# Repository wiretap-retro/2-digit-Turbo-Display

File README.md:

# 2 digit Turbo Display
This project is a ATTiny85-based turbo display for retro PC's. It displays 2 digits, for use in 8088 to 486 systems.

## Intro
I was wanting to do an ATTiny85 project and came up with a small 2-digit turbo display for use in my Intel 486 retro gaming PC. This design is pretty simple, easy to build and easy to program. If you have a dead turbo display or your case is missing one, this might be the right fit, as I have tested it on 3 different cases I have and it fits perfect into all of them. Mounting holes are different in nearly every case, so another mounting method may be necessary depending on your situation.
<br /><br />
Demo Video: https://youtu.be/Jka8PfParP4

## Building
* Order the PCB through your PCB fab of choice. (JLCPCB, PCBway, OSH Park, etc.)
* Order the components as listed in the BOM. Substitutions may be necessary depending on the chip/component shortages.
* On the back side and front side, solder the surface mount components first. Pay close attention to the orientation of the SOIC chips, as they are reversed from each other on the right and left.
* On the back side, solder the through-hole components next. I recommend using a socket for the ATTiny85 so you can easily install/remove it for programming.
* On the front side, solder the LED 7-segment displays.
* Soldering complete. Go to the Programming section below.

## Programming
I have included the turbo.ino file as an example. In the main program loop, you can change the "normal" and "turbo" variables to any 2 digit number to match the needs of your particular CPU speeds. The code is pretty well commented, so you can play around with it, adjust delays, make a startup animation, etc. To program the ATTiny85, you can look at one of the hundreds of guides online. For mine, I used a breadboard and another Arduino to do so. After it is programmed, place it in the DIP-8 socket of the turbo display PCB.

## Installation
* As noted in the intro section, this was designed to fit in the Baby-AT cases I have. It seems there was no standard back in the day for making these turbo displays or mounting them, so each case can be different. The digit size fits all mine that have 2-digit display holes, and at least one mounting hole fits on two of the cases. Only one screw is really necessary anyway since it is so small and light. You can secure it in your case with various methods. (tape, blu tack, 3d printed clip, etc.)
* Once mounted in the case, connect the 5V power to a Berg/Molex-->2x2.54mm header. 
* Connect the Turbo LED on your case to the TLED OUT pins.
* Use a female to female cable with 2x2.54mm connectors at each end to connect the motherboard's Turbo LED pins to the turbo display board's TLED IN. These are commonly found on Aliexpress, Amazon, and Ebay for use in Arduino/RPi projects.
* The turbo switch on your case should be connected to the computer's motherboard Turbo Switch pins.
* Turn on the PC and test it out!

## Design Notes
The design takes into account that your motherboard has turbo LED pins to drive switching of this display. I found this to be the most common feature among all motherboards, from the 8088 to 486. I probably own 25 different boards of this era, and they all have the pins to drive a turbo LED. This is the most universal design I could come up with.

## Other
This is an open source project. Feel free to do what you want with it.

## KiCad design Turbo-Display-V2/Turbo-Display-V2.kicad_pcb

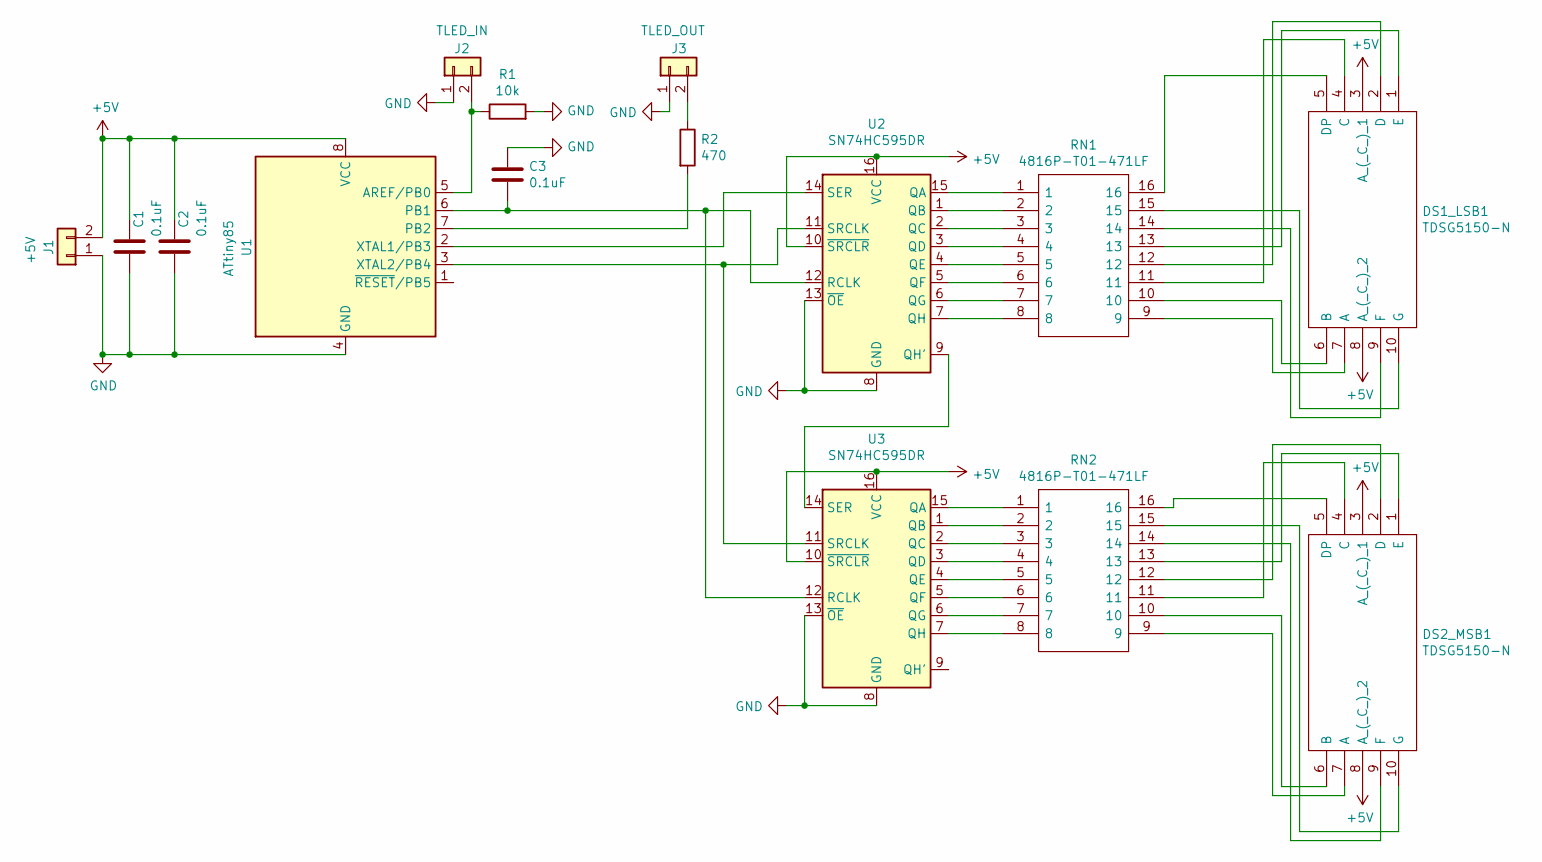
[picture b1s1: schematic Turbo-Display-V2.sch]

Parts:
C1, C2: 0.1uF; C_1206_3216Metric_Pad1.42x1.75mm_HandSolder
C3: 0.1uF; C_0805_2012Metric_Pad1.15x1.40mm_HandSolder
DS1_LSB1, DS2_MSB1: TDSG5150-N; TDSG5150N; Mouser Part Number 78-TDSG5150-N
J1: +5V; PinHeader_1x02_P2.54mm_Vertical
J2: TLED_IN; PinHeader_1x02_P2.54mm_Vertical
J3: TLED_OUT; PinHeader_1x02_P2.54mm_Vertical
R1: 10k; R_0805_2012Metric_Pad1.15x1.40mm_HandSolder
R2: 470; R_0805_2012Metric_Pad1.15x1.40mm_HandSolder
RN1, RN2: 4816P-T01-471LF; SOIC127P762X240-16N; Mouser Part Number 652-4816P-T1LF-470
U1: ATtiny85; DIP-8_W7.62mm
U2, U3: SN74HC595DR; SOIC127P600X175-16N

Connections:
+5V: C1.1, C2.1, DS1_LSB1.3 (A_(_C_)_1), DS1_LSB1.8 (A_(_C_)_2), DS2_MSB1.3 (A_(_C_)_1), DS2_MSB1.8 (A_(_C_)_2), J1.2, U1.8 (VCC), U2.10 (~SRCLR), U2.16 (VCC), U3.10 (~SRCLR), U3.16 (VCC)
GND: C1.2, C2.2, C3.1, J1.1, J2.1, J3.1, R1.2, U1.4 (GND), U2.8 (GND), U2.13 (~OE), U3.8 (GND), U3.13 (~OE)
unnamed: C3.2, U1.6 (PB1), U2.12 (RCLK), U3.12 (RCLK)
unnamed: DS1_LSB1.1 (E), RN1.13
unnamed: DS1_LSB1.2 (D), RN1.12
unnamed: DS1_LSB1.4 (C), RN1.11
unnamed: DS1_LSB1.5 (DP), RN1.16
unnamed: DS1_LSB1.6 (B), RN1.10
unnamed: DS1_LSB1.7 (A), RN1.9
unnamed: DS1_LSB1.9 (F), RN1.14
unnamed: DS1_LSB1.10 (G), RN1.15
unnamed: DS2_MSB1.1 (E), RN2.13
unnamed: DS2_MSB1.2 (D), RN2.12
unnamed: DS2_MSB1.4 (C), RN2.11
unnamed: DS2_MSB1.5 (DP), RN2.16
unnamed: DS2_MSB1.6 (B), RN2.10
unnamed: DS2_MSB1.7 (A), RN2.9
unnamed: DS2_MSB1.9 (F), RN2.14
unnamed: DS2_MSB1.10 (G), RN2.15
unnamed: J2.2, R1.1, U1.5 (AREF/PB0)
unnamed: J3.2, R2.1
unnamed: R2.2, U1.7 (PB2)
unnamed: RN1.1, U2.15 (QA)
unnamed: RN1.2, U2.1 (QB)
unnamed: RN1.3, U2.2 (QC)
unnamed: RN1.4, U2.3 (QD)
unnamed: RN1.5, U2.4 (QE)
unnamed: RN1.6, U2.5 (QF)
unnamed: RN1.7, U2.6 (QG)
unnamed: RN1.8, U2.7 (QH)
unnamed: RN2.1, U3.15 (QA)
unnamed: RN2.2, U3.1 (QB)
unnamed: RN2.3, U3.2 (QC)
unnamed: RN2.4, U3.3 (QD)
unnamed: RN2.5, U3.4 (QE)
unnamed: RN2.6, U3.5 (QF)
unnamed: RN2.7, U3.6 (QG)
unnamed: RN2.8, U3.7 (QH)
unnamed: U1.2 (XTAL1/PB3), U2.14 (SER)
unnamed: U1.3 (XTAL2/PB4), U2.11 (SRCLK), U3.11 (SRCLK)
unnamed: U2.9 (QH'), U3.14 (SER)

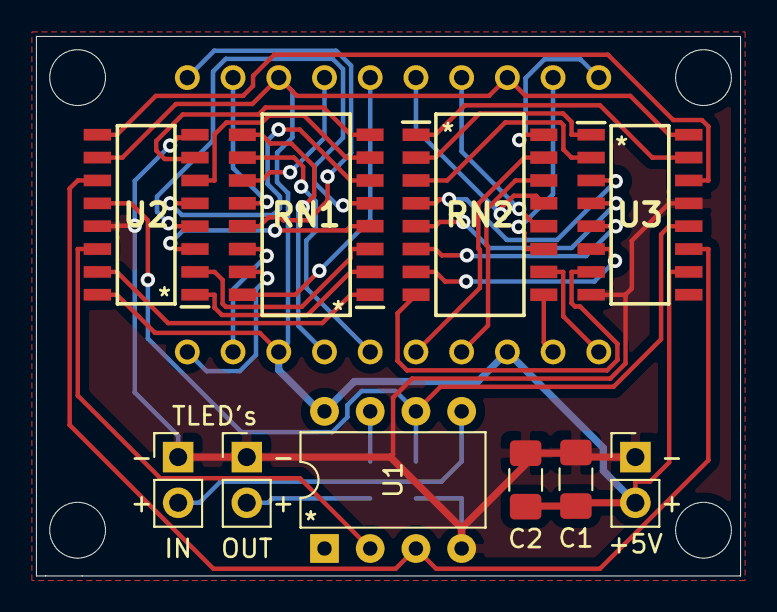
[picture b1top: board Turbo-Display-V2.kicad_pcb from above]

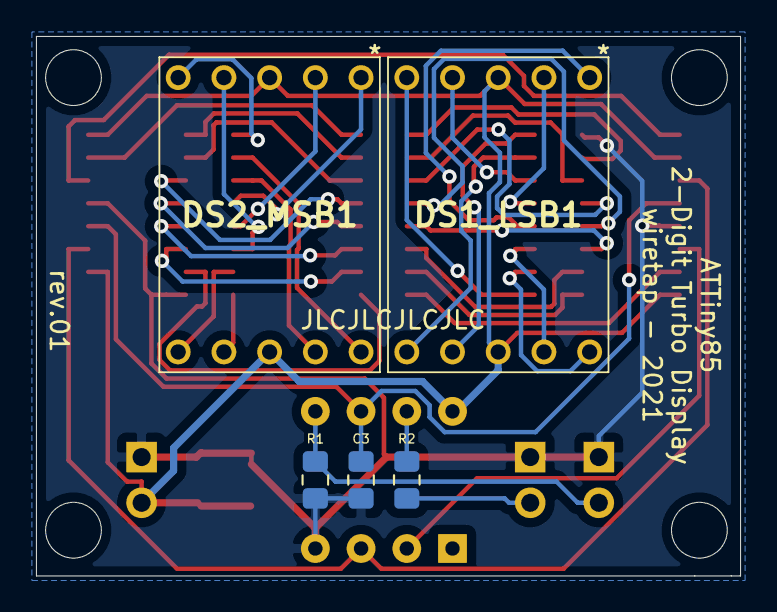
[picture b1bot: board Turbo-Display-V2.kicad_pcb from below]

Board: 2 copper layers, 39.1 x 30.0 mm, 15 parts (5 on the bottom side), 41 nets.

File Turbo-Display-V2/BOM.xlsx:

ref | value | footprint | description
C1, C2 | 0.1uF | Capacitor_SMD:C_1206_3216Metric_Pad1.42x1.75mm_HandSolder | Unpolarized capacitor
C3 | 0.1uF | Capacitor_SMD:C_0805_2012Metric_Pad1.15x1.40mm_HandSolder | Unpolarized capacitor
DS1, DS2 | TDSG5150-N | TDSG5150N | LED Displays & Accessories 7-Seg Green 13 mm Common anode
J1, J2, J3 | 2x1 Pin Header | Connector_PinHeader_2.54mm:PinHeader_1x02_P2.54mm_Vertical | Generic connector, single row, 01x02, script generated (kicad-library-utils/sch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
R1 | 10k | Resistor_SMD:R_0805_2012Metric_Pad1.15x1.40mm_HandSolder | Resistor
R2 | 470 | Resistor_SMD:R_0805_2012Metric_Pad1.15x1.40mm_HandSolder | Resistor
RN1, RN2 | 4816P-T01-471LF | SOIC127P762X240-16N | Res Thick Film NET 470 Ohm 2% 1.28W +/-100ppm/C ISOL Molded 16-Pin SOM Gull Win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
U1 | ATtiny85 | Package_DIP:DIP-8_W7.62mm | 20MHz, 8kB Flash, 512B SRAM, 512B EEPROM, debugWIRE, DIP-8
U2, U3 | SN74HC595DR | SamacSys_Parts:SOIC127P600X175-16N | 8-bit serial in/out Shift Register 3-State Outputs
